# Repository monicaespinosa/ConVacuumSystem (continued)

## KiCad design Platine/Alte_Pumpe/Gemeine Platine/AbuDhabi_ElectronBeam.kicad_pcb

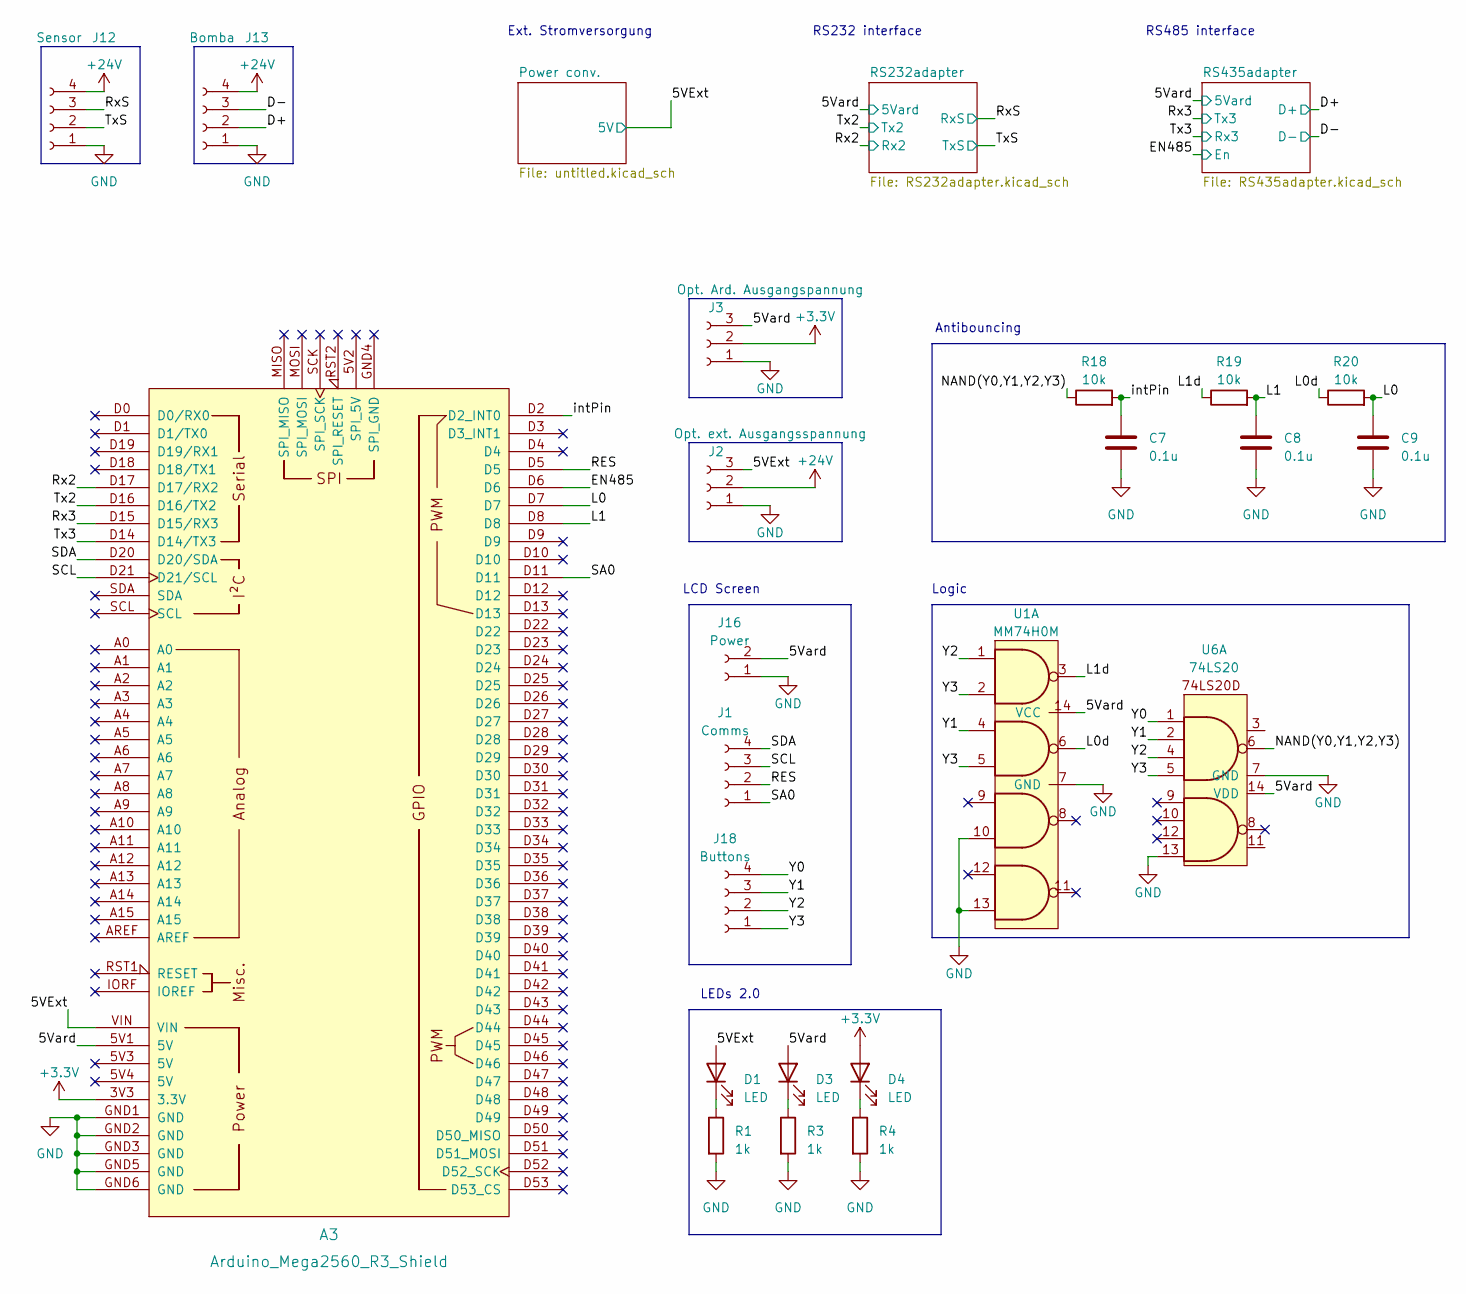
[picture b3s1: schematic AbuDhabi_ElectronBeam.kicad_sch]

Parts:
A3: Arduino_Mega2560_R3_Shield
C7, C8, C9: 0.1u; C_0603_1608Metric
D1, D3, D4: LED; LED_0603_1608Metric_Pad1.05x0.95mm_HandSolder
J1: Comms; PinSocket_1x04_P2.54mm_Vertical
J2: Opt. ext. Ausgangsspannung; PinSocket_1x03_P2.54mm_Vertical
J3: Opt. Ard. Ausgangspannung; PinSocket_1x03_P2.54mm_Vertical
J12: Sensor; JST_EH_B4B-EH-A_1x04_P2.50mm_Vertical
J13: Bomba; JST_EH_B4B-EH-A_1x04_P2.50mm_Vertical
J16: Power; PinSocket_1x02_P2.54mm_Vertical
J18: Buttons; PinSocket_1x04_P2.54mm_Vertical
R1, R3, R4: 1k; R_0603_1608Metric_Pad0.98x0.95mm_HandSolder
R18, R19, R20: 10k; R_0603_1608Metric
U1: MM74H0M; SOIC-14_3.9x8.7mm_P1.27mm
U6: 74LS20; SOIC-14_3.9x8.7mm_P1.27mm

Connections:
+3.3V: A3.3V3 (3.3V), D4.2 (A), J3.2
/5Vard: A3.5V1 (5V), D3.2 (A), J3.3, J16.2, U1.14 (VCC), U6.14 (VDD); also elsewhere on the board
/D+: J13.2; also elsewhere on the board
/D-: J13.3; also elsewhere on the board
/EN485: A3.D6; also elsewhere on the board
/L0: A3.D7, C9.1, R20.2
/L0d: R20.1, U1.6
/L1: A3.D8, C8.1, R19.2
/L1d: R19.1, U1.3
/NAND(Y0,Y1,Y2,Y3): R18.1, U6.6
/RES: A3.D5, J1.2
/Rx2: A3.D17 (D17/RX2); also elsewhere on the board
/Rx3: A3.D15 (D15/RX3); also elsewhere on the board
/RxS: J12.3; also elsewhere on the board
/SA0: A3.D11, J1.1
/SCL: A3.D21 (D21/SCL), J1.3
/SDA: A3.D20 (D20/SDA), J1.4
/Tx2: A3.D16 (D16/TX2); also elsewhere on the board
/Tx3: A3.D14 (D14/TX3); also elsewhere on the board
/TxS: J12.2; also elsewhere on the board
/Y0: J18.4, U6.1
/Y1: J18.3, U1.4, U6.2
/Y2: J18.2, U1.1, U6.4
/Y3: J18.1, U1.2, U1.5, U6.5
/intPin: A3.D2 (D2_INT0), C7.1, R18.2
GND: A3.GND1 (GND), A3.GND2 (GND), A3.GND3 (GND), A3.GND5 (GND), A3.GND6 (GND), C7.2, C8.2, C9.2, J2.1, J3.1, J12.1, J13.1, J16.1, R1.2, R3.2, R4.2, U1.7 (GND), U1.10, U1.13, U6.7 (GND), U6.13; also elsewhere on the board
unnamed: D1.1 (K), R1.1
unnamed: D3.1 (K), R3.1
unnamed: D4.1 (K), R4.1

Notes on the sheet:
Logic
LCD Screen
Ext. Stromversorgung
RS485 interface
Antibouncing
RS232 interface
LEDs 2.0

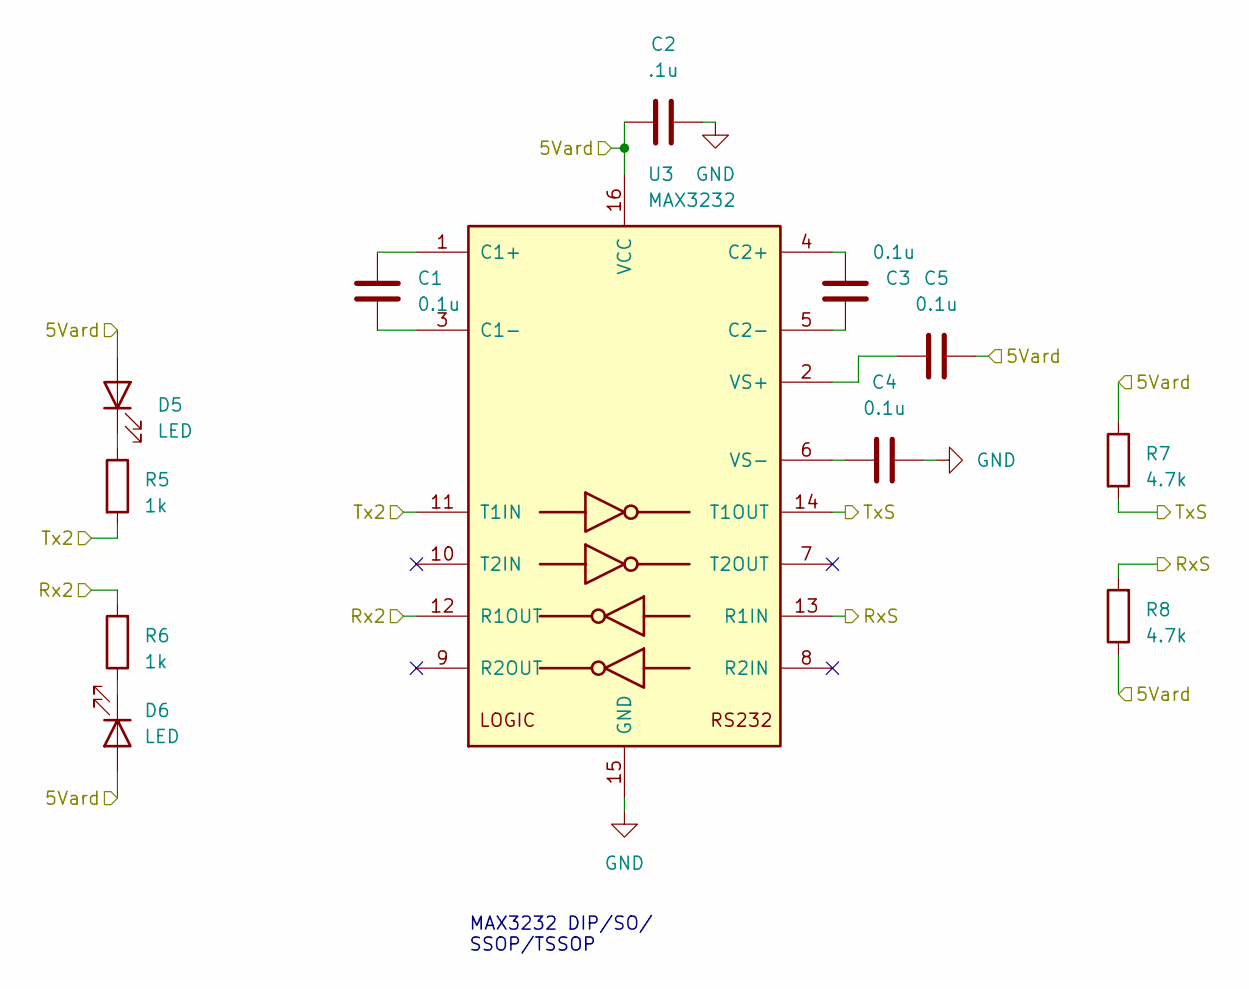
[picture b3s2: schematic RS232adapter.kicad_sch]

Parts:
C1, C3, C4, C5: 0.1u; C_0603_1608Metric
C2: .1u; C_0603_1608Metric
D5: LED; LED_0603_1608Metric
D6: LED; LED_0603_1608Metric_Pad1.05x0.95mm_HandSolder
R5, R6: 1k; R_0603_1608Metric
R7, R8: 4.7k; R_0603_1608Metric
U3: MAX3232; SOIC-16_3.9x9.9mm_P1.27mm

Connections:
/5Vard: C2.1, C5.2, D5.2 (A), D6.2 (A), R7.1, R8.1, U3.16 (VCC); also elsewhere on the board
/Rx2: R6.2, U3.12 (R1OUT); also elsewhere on the board
/RxS: R8.2, U3.13 (R1IN); also elsewhere on the board
/Tx2: R5.2, U3.11 (T1IN); also elsewhere on the board
/TxS: R7.2, U3.14 (T1OUT); also elsewhere on the board
GND: C2.2, C4.2, U3.15 (GND); also elsewhere on the board
unnamed: D5.1 (K), R5.1
unnamed: D6.1 (K), R6.1
unnamed: C1.1, U3.1 (C1+)
unnamed: C1.2, U3.3 (C1-)
unnamed: C3.1, U3.4 (C2+)
unnamed: C3.2, U3.5 (C2-)
unnamed: C5.1, U3.2 (VS+)
unnamed: C4.1, U3.6 (VS-)

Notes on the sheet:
MAX3232 DIP/SO/ SSOP/TSSOP

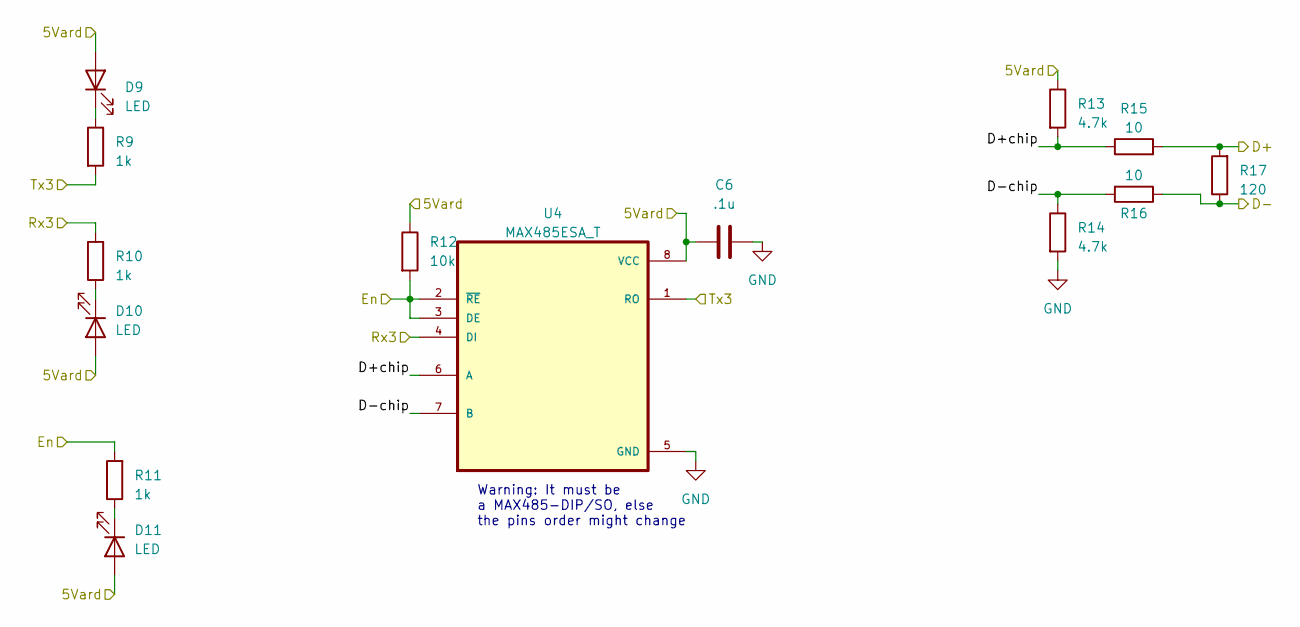
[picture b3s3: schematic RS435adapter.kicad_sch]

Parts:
C6: .1u; C_0603_1608Metric
D9, D10, D11: LED; LED_0603_1608Metric
R9, R10, R11: 1k; R_0603_1608Metric
R12: 10k; R_0603_1608Metric
R13, R14: 4.7k; R_0603_1608Metric
R15, R16: 10; R_0603_1608Metric
R17: 120; R_0603_1608Metric
U4: MAX485ESA_T; SOIC127P600X175-8N

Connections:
/5Vard: C6.1, D9.2 (A), D10.2 (A), D11.2 (A), R12.1, R13.1, U4.8 (VCC); also elsewhere on the board
/D+: R15.2, R17.2; also elsewhere on the board
/D-: R16.1, R17.1; also elsewhere on the board
/EN485: R11.2, R12.2, U4.2 (~RE), U4.3 (DE); also elsewhere on the board
/RS435adapter/D+chip: R13.2, R15.1, U4.6 (A)
/RS435adapter/D-chip: R14.1, R16.2, U4.7 (B)
/Rx3: R9.2, U4.1 (RO); also elsewhere on the board
/Tx3: R10.2, U4.4 (DI); also elsewhere on the board
GND: C6.2, R14.2, U4.5 (GND); also elsewhere on the board
unnamed: D9.1 (K), R9.1
unnamed: D10.1 (K), R10.1
unnamed: D11.1 (K), R11.1

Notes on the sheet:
Warning: It must be a MAX485-DIP/SO, else the pins order might change

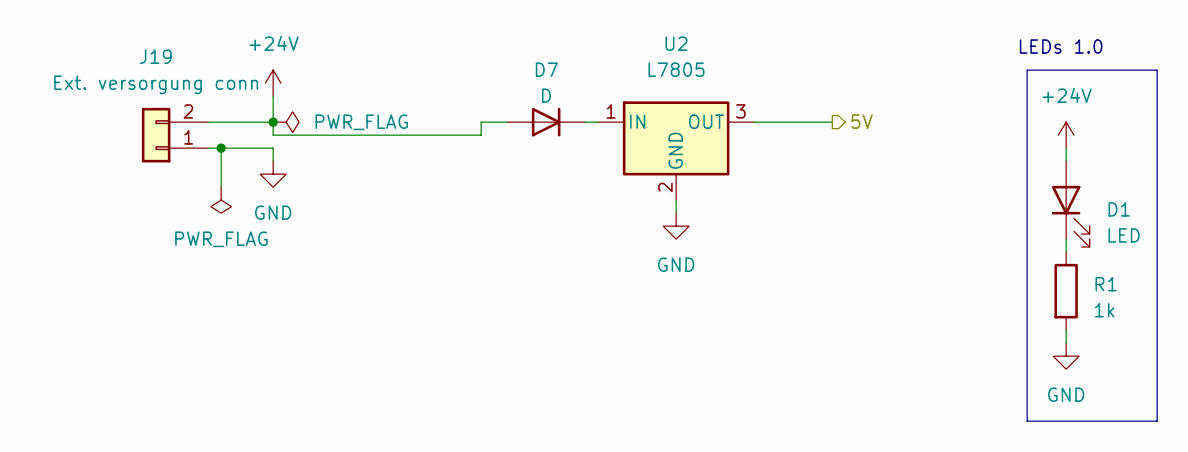
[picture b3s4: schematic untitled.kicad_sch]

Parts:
D1: LED; LED_0603_1608Metric_Pad1.05x0.95mm_HandSolder
D7: D; LED_0603_1608Metric_Pad1.05x0.95mm_HandSolder
J19: Ext. versorgung conn; JST_EH_B2B-EH-A_1x02_P2.50mm_Vertical
R1: 1k; R_0603_1608Metric
U2: L7805; TO-220-3_Vertical

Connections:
GND: J19.1, R1.2, U2.2 (GND); also elsewhere on the board
unnamed: D1.1 (K), R1.1
unnamed: D7.1 (K), U2.1 (IN)

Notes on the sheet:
LEDs 1.0

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
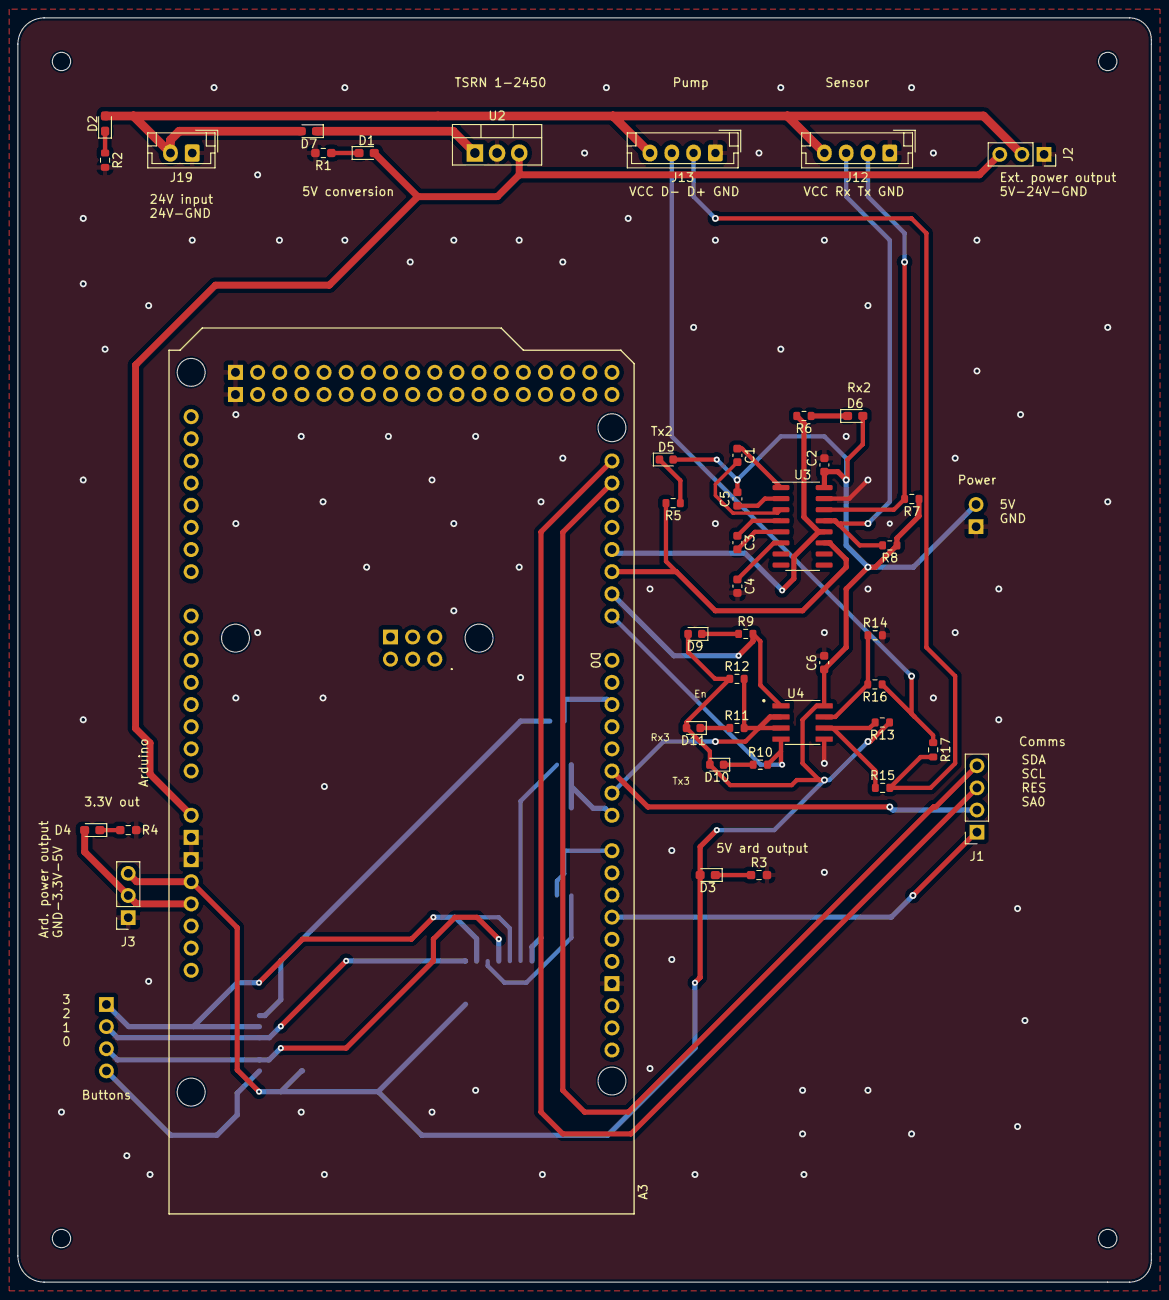
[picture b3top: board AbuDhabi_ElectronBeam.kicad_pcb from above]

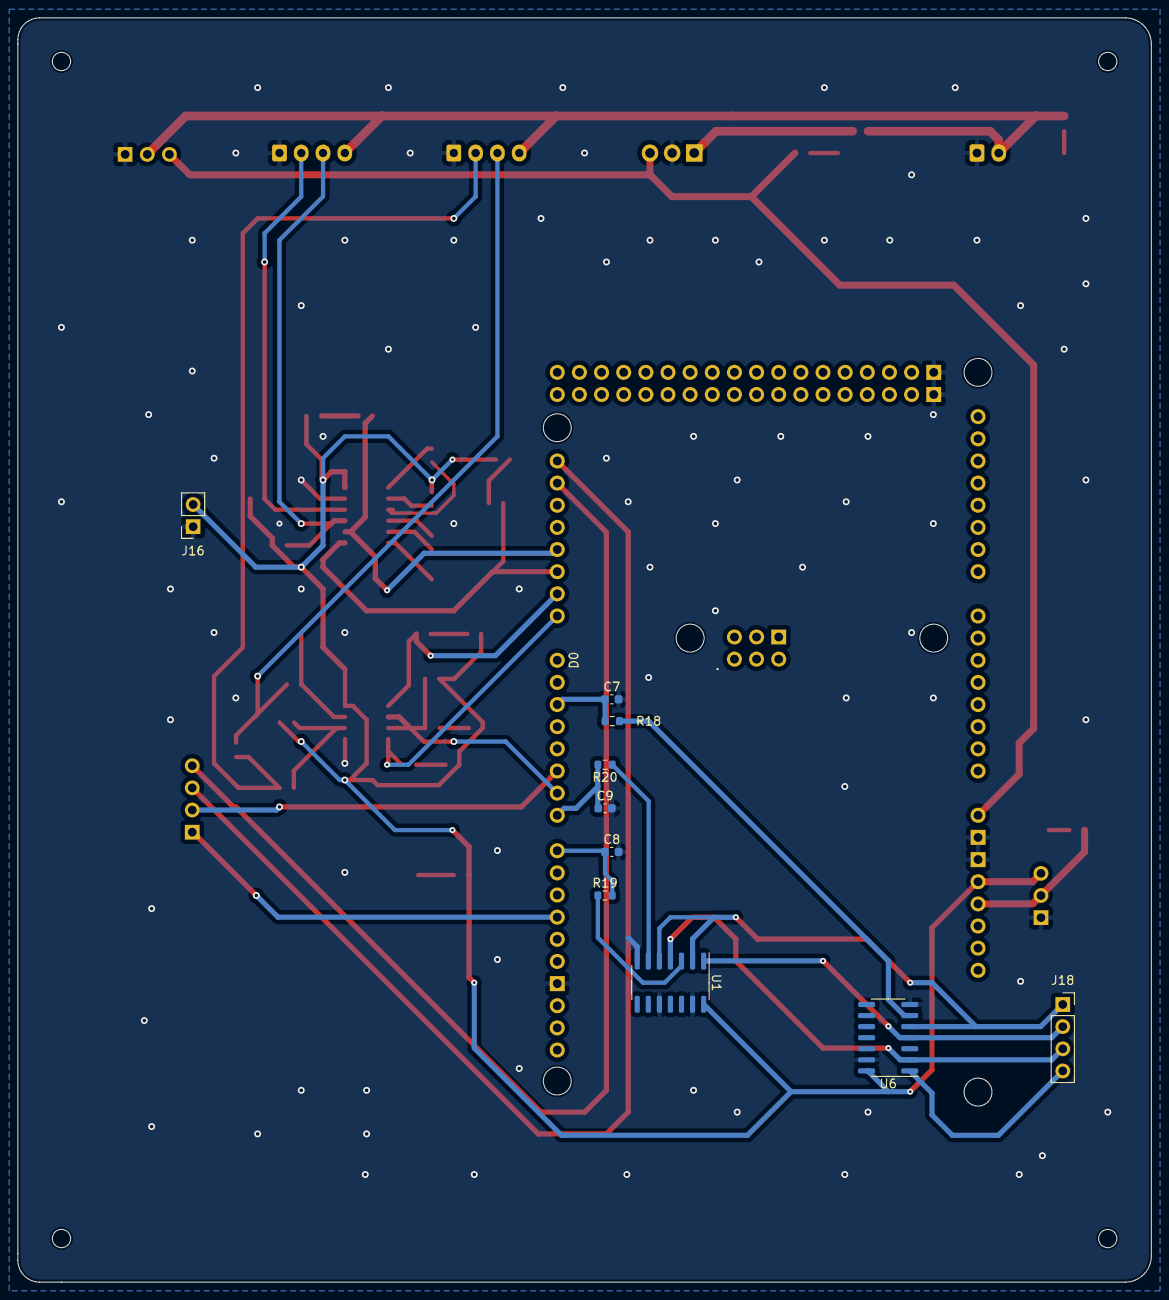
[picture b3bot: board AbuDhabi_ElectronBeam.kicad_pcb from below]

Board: 2 copper layers, 130.0 x 145.0 mm, 53 parts (11 on the bottom side), 46 nets.

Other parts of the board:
D2: LED; LED_0603_1608Metric_Pad1.05x0.95mm_HandSolder
R2: 1k; R_0603_1608Metric

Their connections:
GND: R2.2; also elsewhere on the board
unnamed: D2.1 (K), R2.1

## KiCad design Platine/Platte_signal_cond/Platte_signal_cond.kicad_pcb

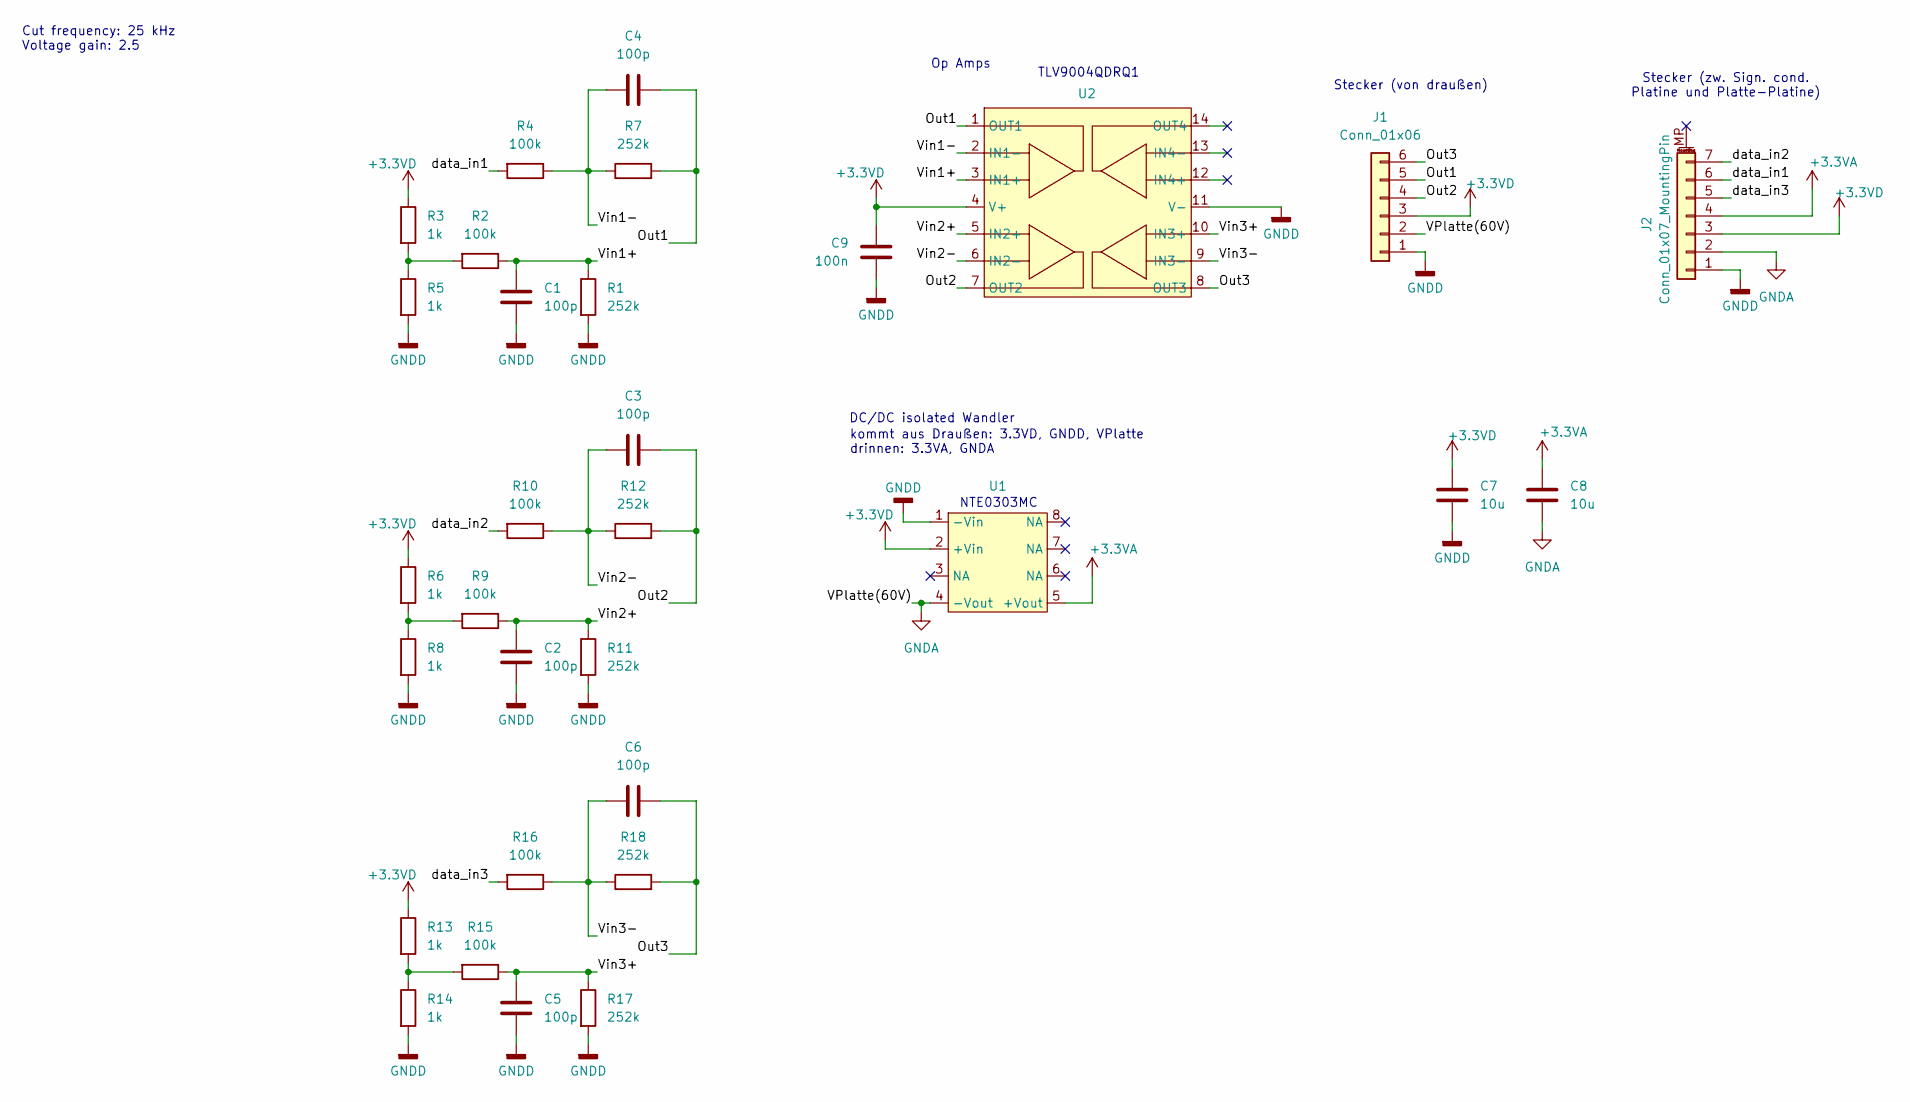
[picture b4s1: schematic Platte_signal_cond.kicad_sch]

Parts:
C1, C2, C3, C4, C5, C6: 100p; C_0603_1608Metric_Pad1.08x0.95mm_HandSolder
C7, C8: 10u; C_0603_1608Metric_Pad1.08x0.95mm_HandSolder
C9: 100n; C_0603_1608Metric_Pad1.08x0.95mm_HandSolder
J1: Conn_01x06; JST_EH_B6B-EH-A_1x06_P2.50mm_Vertical
J2: Conn_01x07_MountingPin; JST_GH_BM07B-GHS-TBT_1x07-1MP_P1.25mm_Vertical
R1, R7, R11, R12, R17, R18: 252k; R_0603_1608Metric_Pad0.98x0.95mm_HandSolder
R2, R4, R9, R10, R15, R16: 100k; R_0603_1608Metric_Pad0.98x0.95mm_HandSolder
R3, R5, R6, R8, R13, R14: 1k; R_0603_1608Metric_Pad0.98x0.95mm_HandSolder
U1: SMDIP-8_W9.53mm
U2: SOIC-14_3.9x8.7mm_P1.27mm

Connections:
+3.3VA: C8.2, J2.4, U1.5 (+Vout)
+3.3VD: C7.2, C9.2, J1.3, J2.3, R3.1, R6.1, R13.1, U1.2 (+Vin), U2.4 (V+)
/Out1: C4.1, J1.5, R7.2, U2.1 (OUT1)
/Out2: C3.1, J1.4, R12.2, U2.7 (OUT2)
/Out3: C6.1, J1.6, R18.2, U2.8 (OUT3)
/Vin1+: C1.2, R1.1, R2.1, U2.3 (IN1+)
/Vin1-: C4.2, R4.1, R7.1, U2.2 (IN1-)
/Vin2+: C2.2, R9.1, R11.1, U2.5 (IN2+)
/Vin2-: C3.2, R10.1, R12.1, U2.6 (IN2-)
/Vin3+: C5.2, R15.1, R17.1, U2.10 (IN3+)
/Vin3-: C6.2, R16.1, R18.1, U2.9 (IN3-)
/data_in1: J2.6, R4.2
/data_in2: J2.7, R10.2
/data_in3: J2.5, R16.2
GNDA: C8.1, J1.2, J2.2, U1.4 (-Vout)
GNDD: C1.1, C2.1, C5.1, C7.1, C9.1, J1.1, J2.1, R1.2, R5.2, R8.2, R11.2, R14.2, R17.2, U1.1 (-Vin), U2.11 (V-)
unnamed: R2.2, R3.2, R5.1
unnamed: R6.2, R8.1, R9.2
unnamed: R13.2, R14.1, R15.2

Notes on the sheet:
kommt aus Draußen: 3.3VD, GNDD, VPlatte drinnen: 3.3VA, GNDA
Cut frequency: 25 kHz Voltage gain: 2.5
DC/DC isolated Wandler
TLV9004QDRQ1
Op Amps
Stecker (zw. Sign. cond. Platine und Platte-Platine)
NTE0303MC
Stecker (von draußen)

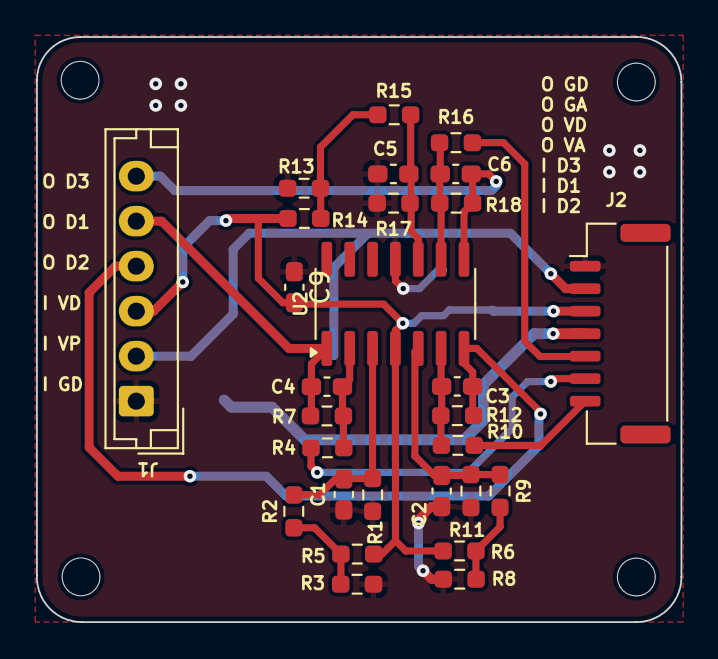
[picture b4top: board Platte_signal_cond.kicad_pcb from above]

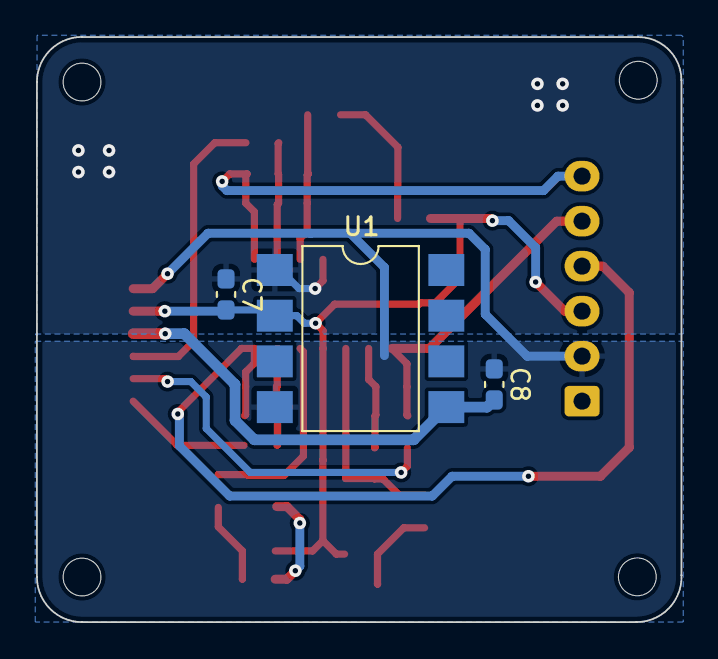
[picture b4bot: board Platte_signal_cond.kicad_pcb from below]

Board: 2 copper layers, 35.8 x 32.5 mm, 35 parts (3 on the bottom side), 19 nets.

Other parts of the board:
M1, M2, M3, M4: MountingHole_2.1mm

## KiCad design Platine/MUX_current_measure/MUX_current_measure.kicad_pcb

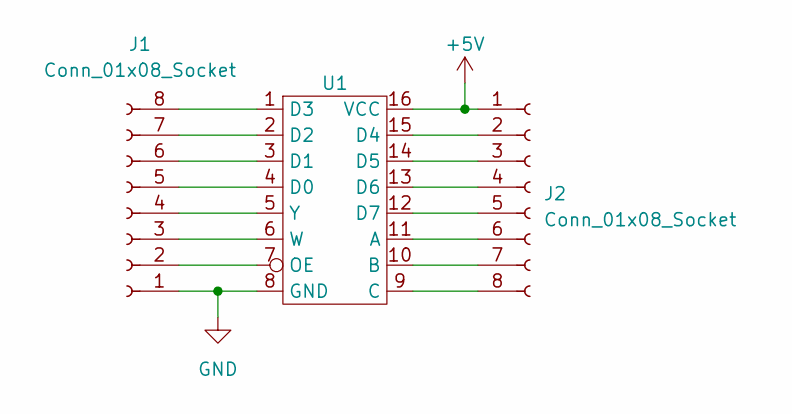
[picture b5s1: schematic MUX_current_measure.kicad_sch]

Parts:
J1, J2: Conn_01x08_Socket; PinHeader_1x08_P2.54mm_Vertical
U1: TSSOP-16_4.4x5mm_P0.65mm

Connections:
+5V: J2.1, U1.16 (VCC)
GND: J1.1, U1.8 (GND)
unnamed: J1.2, U1.7 (OE)
unnamed: J1.3, U1.6 (W)
unnamed: J1.4, U1.5 (Y)
unnamed: J1.5, U1.4 (D0)
unnamed: J1.6, U1.3 (D1)
unnamed: J1.7, U1.2 (D2)
unnamed: J1.8, U1.1 (D3)
unnamed: J2.2, U1.15 (D4)
unnamed: J2.3, U1.14 (D5)
unnamed: J2.4, U1.13 (D6)
unnamed: J2.5, U1.12 (D7)
unnamed: J2.6, U1.11 (A)
unnamed: J2.7, U1.10 (B)
unnamed: J2.8, U1.9 (C)

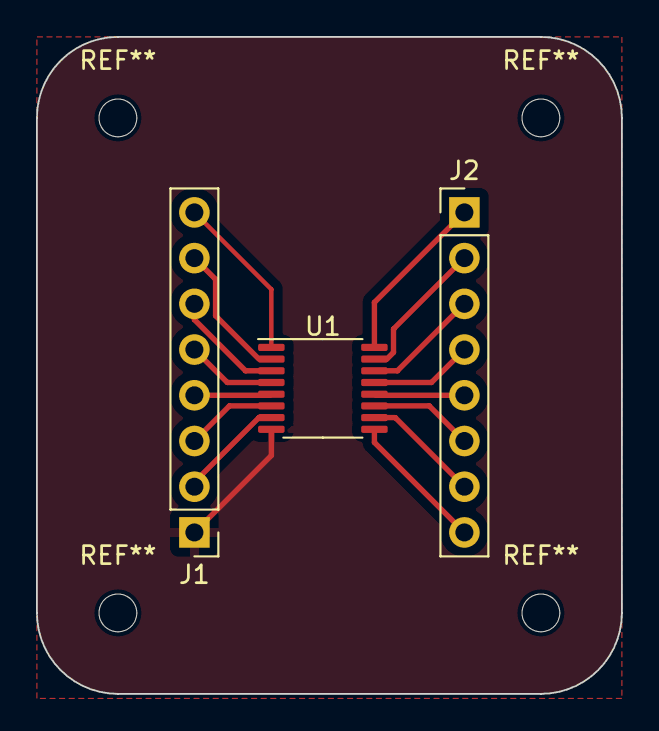
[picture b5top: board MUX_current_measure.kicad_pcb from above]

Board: 2 copper layers, 32.5 x 36.5 mm, 3 parts (0 on the bottom side), 16 nets.

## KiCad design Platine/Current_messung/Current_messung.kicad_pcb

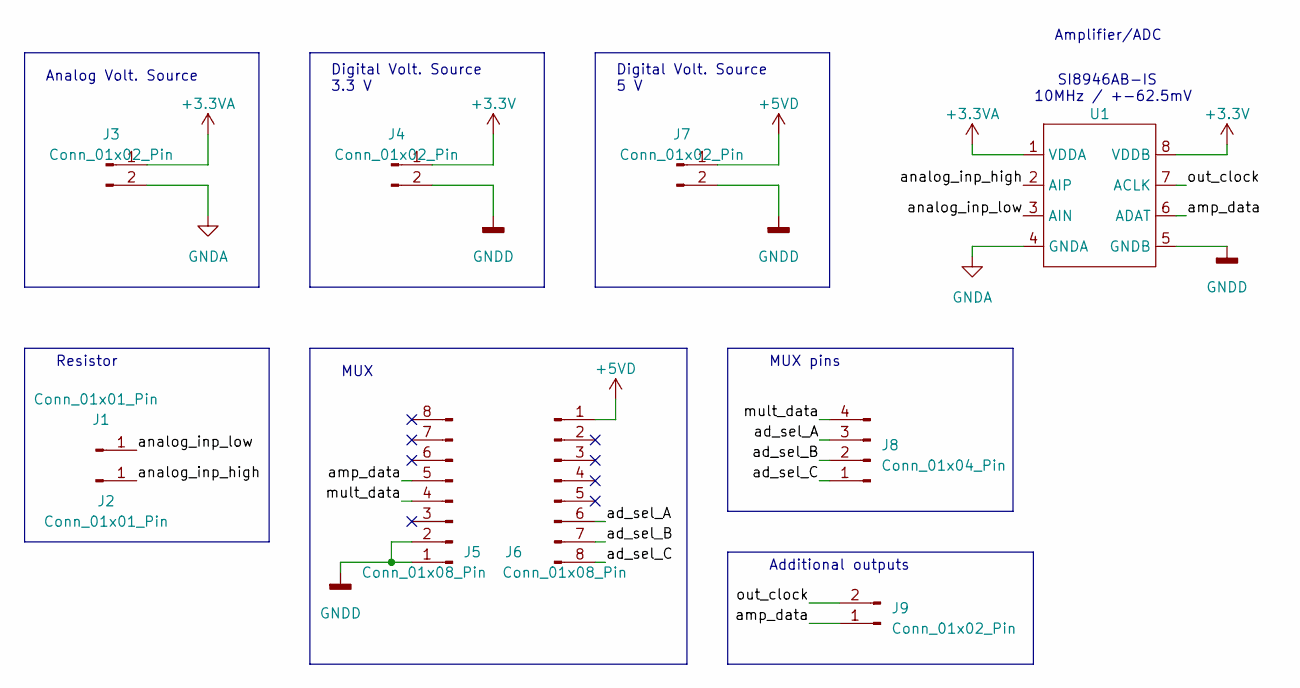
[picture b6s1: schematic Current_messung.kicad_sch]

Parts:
J1, J2: Conn_01x01_Pin; PinHeader_1x01_P2.54mm_Vertical
J3, J4, J7, J9: Conn_01x02_Pin; PinHeader_1x02_P2.54mm_Vertical
J5, J6: Conn_01x08_Pin; PinHeader_1x08_P2.54mm_Vertical
J8: Conn_01x04_Pin; PinHeader_1x04_P2.54mm_Vertical
U1: SOP-8_3.9x4.9mm_P1.27mm

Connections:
+3.3V: J4.1, U1.8 (VDDB)
+3.3VA: J3.1, U1.1 (VDDA)
+5VD: J6.1, J7.1
/ad_sel_A: J6.6, J8.3
/ad_sel_B: J6.7, J8.2
/ad_sel_C: J6.8, J8.1
/amp_data: J5.5, J9.1, U1.6 (ADAT)
/analog_inp_high: J2.1, U1.2 (AIP)
/analog_inp_low: J1.1, U1.3 (AIN)
/mult_data: J5.4, J8.4
/out_clock: J9.2, U1.7 (ACLK)
GNDA: J3.2, U1.4 (GNDA)
GNDD: J4.2, J5.1, J5.2, J7.2, U1.5 (GNDB)

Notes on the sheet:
Resistor
Additional outputs
Amplifier/ADC
SI8946AB-IS 10MHz / +-62.5mV
MUX pins
Digital Volt. Source 5 V
Digital Volt. Source 3.3 V
Analog Volt. Source
MUX

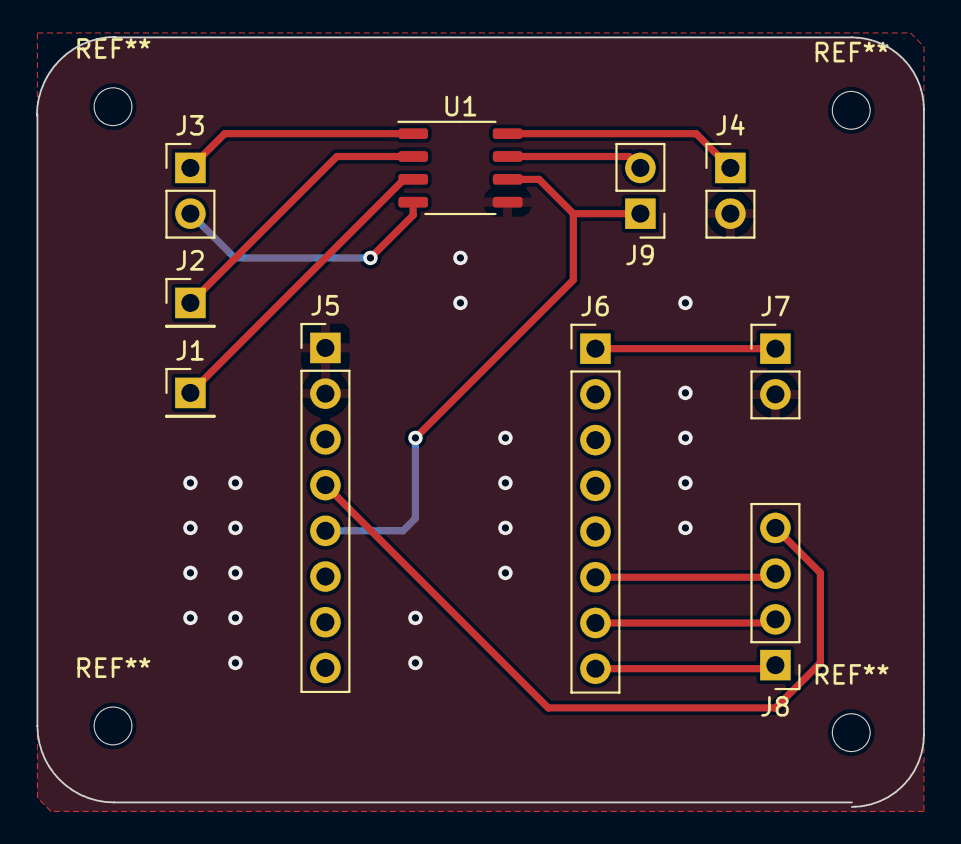
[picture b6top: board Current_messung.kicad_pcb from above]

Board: 2 copper layers, 49.3 x 42.8 mm, 10 parts (0 on the bottom side), 13 nets.

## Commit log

2023-12-28 Create README.md
    general description of the arduino program.
    For now, the program is not divided into libraries and it will be uploaded in function parts and UI parts.
2023-12-28 Create PumpComm_SensorRead.ino
    General program of the functionality of the control unit. Here it is a block of code, the idea is to separate it into libraries.
2024-01-15 Create PumpScreenUI.ino
    First functions of the screen UI. This is a display of the data acquire from the pump comm and the sensor.
2024-01-15 Changing screen arduino code so it works with the board
2024-01-29 Interruption code started
    Initial interruption code, more tests need to be done
2024-02-05 Interruption code tested. It works.
2024-02-16 Create the library for the pressure sensor ITR090 - RS232Comm protocol
2024-02-19 Nothing
2024-02-26 Changes on screen code
2024-02-26 Ergänzung der Projekte der Platinen.
2024-02-26 Small change in schematic
2024-02-26 Interruption Test code changed, it works
2024-03-04 State Maschine Programmierung v.1
2024-03-04 Testing selecting arrow part 1
2024-03-04 Other tests with the screen code
2024-03-04 Screen code ready (for now)
2024-03-06 DCU library / turbo pump library done. requires testing. compiles without errors or warnings
2024-03-07 Test function for the arrown added to the LCD code
2024-03-08 turbopump library tested and corrected. works until this point, maybe further changes
2024-03-08 Delete Arduino/PumpComm_SensorRead directory
    to allow commit
2024-03-11 Merging screen code with control code
2024-03-11 Screen code merged with main code. Still missing to adjust some function imput variables
2024-03-15 Relevant datasheets and documents for the vacuum setup
2024-03-15 Additional info for working with turbopumps
2024-03-15 Code completely merged
2024-03-20 Some changes to the screen code
2024-03-25 Adding comments to sensor ITR 90 library
2024-03-25 same as before
2024-03-25 Code fixed so it reads correctly the ITR90 sensor
2024-03-26 adding function to turn on/off the pumps through the lcd screen
2024-04-08 starting virtual screen with python
2024-04-21 Changes to python code
2024-04-22 nthng
2024-04-22 Finished screens in python, now arranging char array from arduino to python
2024-04-23 some changes
2024-04-23 python code almost ready
2024-04-24 the code works
2024-06-18 added command to indicate the ITR090 sensor that the pressure units are mbar
2024-06-21 Added Draft2.asc
2024-08-23 RunningMoreSims.md
2024-09-04 EndOfSimulations.md
2024-09-11 Viel hat geändert
2024-09-11 virtualler Bildschirm changes
2024-09-13 Nichts
2024-09-18 Adding a CST simulation
2024-09-18 Adding CST simulation with filled cylinder
2024-09-18 Adding Hohlzylinider CST simulation
2024-09-20 Uploading PCB of the current measuring plate
2024-09-23 Changes to plate PCB
2024-09-23 Plate PCB almost done
2024-09-25 Few changes plate PCB
2024-09-25 small changes
2024-09-25 Adding now RC filter and DC Converter to Plate PCB
2024-09-30 Nothing special
2024-10-01 adding signal conditioning phase to plate PCB
2024-10-02 not much
2024-10-03 Results of changing the voltage on the plate on README file
2024-10-03 plate pcb almost finished
2024-10-04 Removing CST simulations because of weight, theyre now in the folder outside the repo
2024-10-07 Adding footprints to signal conditioning PCB and placing components
2024-10-08 PCBs almost finished
2024-10-09 PCBs completely finished
2024-10-09 Mit Robin geredet, ein paar Veränderung gemacht
2024-10-10 LTSpice sim
2024-10-21 LTSpice simulation almost done
2024-10-21 4 clapton coils simulation result.md
2024-10-21 LTSpice simulation done. Changing now schematics and PCB
2024-10-21 nicht so viel
2024-10-23 PCBs ready
2024-10-23 Modifying working frequency in LTSpice and adding extra resistor in pcb
2024-10-24 mit Robin geredet
2024-10-25 Simulation verändert und fertiggemacht
2024-10-29 Final circuits designed. Plate PCB ready, signal cond PCB still in process
2024-10-30 Made a few changes to PCBs and schematics
2024-10-30 Both the PCBs finished
2024-10-31 Small correction. Everything finished
2024-11-05 Better shaping the Plates on the PCB
2024-11-13 Ein paar Änderungen
2025-01-31 All the changes until today
2025-02-06 Updated Arduino code for reading test PCB
2025-02-11 Changes in LTSpice simulations
2025-02-11 corrections on platte PCB
2025-02-11 trying to merge
2025-02-12 Starting with final PCB
2025-02-13 changes in new pcb
2025-02-16 a lot of advance in final PCB
2025-02-18 still need to finish routing
2025-02-18 Almost done with routing
2025-02-19 final PCB finished
2025-02-19 Added grid voltage connector
2025-02-20 Commit before changing PCB connectors, just in case
2025-02-20 Changed connectors according to stock. Added auxiliar projects for printing each PCB, added component list
2025-02-20 bom_list file from kicad added
2025-02-24 adding some matlab simulations and graphs
2025-02-24 trying to merge again
2025-02-28 just committing local changes
2025-02-28 added 3D milling part
2025-03-03 ard code updated
2025-03-09 no idea
2025-03-10 updated Arduino code
2025-03-11 small changes on Arduino code
2025-03-11 added python code for visualizing currents
2025-03-12 made ard code for 1 surface anode
2025-03-12 added capture of measurement
2025-03-20 Vortrag Vorlage
